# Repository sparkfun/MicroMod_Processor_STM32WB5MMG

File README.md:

SparkFun MicroMod Processor Board - STM32WB5MMG 
========================================

[*MicroMod Processor Board - STM32WB5MMG (DEV-21438)*](https://www.sparkfun.com/products/21438)

The MicroMod STM32WB5MMG Processor expands on SparkFun&apos;s MicroMod ST product line with a powerful combination of computing and wireless capabilities all on one Processor. The STM32WB5MMG from STMicroelectronics<sup>&trade;</sup> is an ultra-low power microcontroller that combines a pair of Arm<sup>&reg;</sup> Cortex<sup>&reg;</sup> processors; a Cortex-M4 processor for primary computing and a Cortex-M0 to run the 2.4 GHz radio. The radio is Bluetooth<sup>&reg;</sup> Low Energy 5.3, Zigbee<sup>&reg;</sup> 3.0, and OpenThread certified.

Repository Contents
-------------------

* **/Documentation** - Data sheets, additional product information
* **/Firmware** - Example code 
* **/Hardware** - Eagle design files (.brd, .sch)
* **/Production** - Production panel files (.brd)

Documentation
--------------
* **[Hookup Guide](https://learn.sparkfun.com/tutorials/micromod-stm32wb5mmg-hookup-guide)** - Basic hookup guide for the MicroMod Processor Board - STM32WB5MMG .
* **[SparkFun Fritzing repo](https://github.com/sparkfun/Fritzing_Parts)** - Fritzing diagrams for SparkFun products.
* **[SparkFun Graphical Datasheets](https://github.com/sparkfun/Graphical_Datasheets)** -Graphical Datasheets for various SparkFun products.

Product Versions
----------------
* [DEV-21438](https://www.sparkfun.com/products/21438)- MicroMod Processor for the STM32WB5MMG

License Information
-------------------

This product is _**open source**_! 

Please review the LICENSE.md file for license information. 

If you have any questions or concerns on licensing, please contact technical support on our [SparkFun forums](https://forum.sparkfun.com/viewforum.php?f=152).

Distributed as-is; no warranty is given.

- Your friends at SparkFun.

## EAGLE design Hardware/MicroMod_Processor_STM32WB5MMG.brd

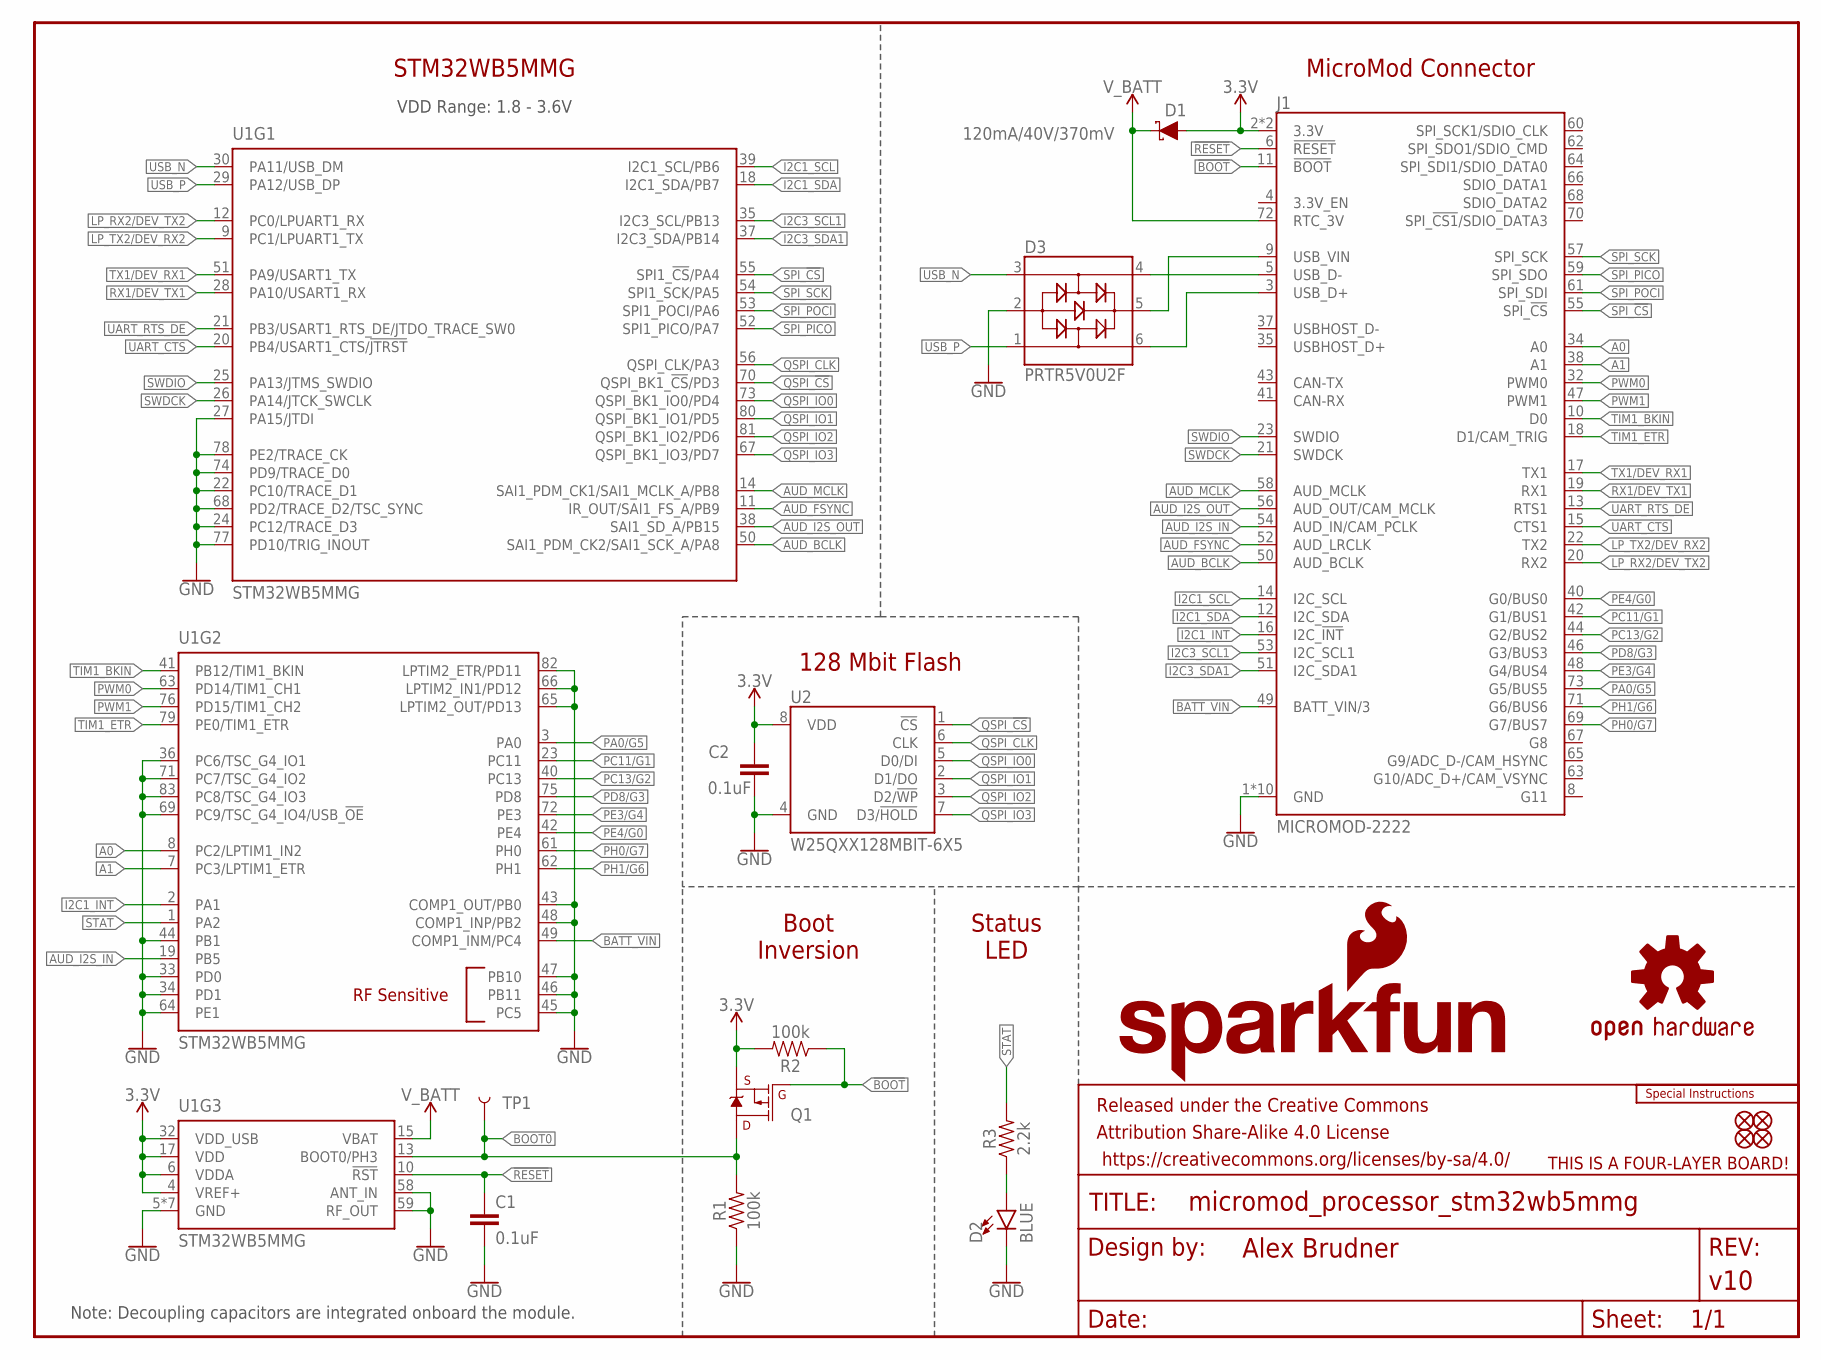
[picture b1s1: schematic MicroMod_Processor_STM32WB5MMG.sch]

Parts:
C1, C2: 0.1uF; 0402-TIGHT
D1: 120mA/40V/370mV; SOD-523
D2: BLUE; LED-0603
D3: PRTR5V0U2F; SOT886
FD1, FD2, FD3, FD4: FIDUCIALUFIDUCIAL; FIDUCIAL-MICRO
FRAME2: FRAME-LETTER; CREATIVE_COMMONS
J1: MICROMOD-2222; M.2-CARD-E-22
LOGO1: FOUR_LAYER_WARNING
LOGO2: OSHW-LOGOMINI; OSHW-LOGO-MINI
LOGO3: SFE_LOGO_NAME_FLAME.1_INCH; SFE_LOGO_NAME_FLAME_.1
LOGO4: SPECIAL_INSTRUCTIONS-ORDERING; ORDERING_INSTRUCTIONS
Q1: 20V/4.2A/52mΩ/1.4W; SOT23-3
R1, R2: 100k; 0402-TIGHT
R3: 2.2k; 0402-TIGHT
TP1: TEST-POINT3; PAD.03X.03
U1: STM32WB5MMG; SIP-LGA86
U2: W25QXX128MBIT-6X5; WSON-8-6X5

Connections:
3.3V: C2.1, D1.A, J1.2 (3.3V), J1.74 (3.3V), Q1.2 (S), R2.2, U1.4 (VREF+), U1.6 (VDDA), U1.17 (VDD), U1.32 (VDD_USB), U2.8 (VDD)
!BOOT!: J1.11 (!BOOT!), Q1.1 (G), R2.1
!RESET!: C1.1, J1.6 (!RESET!), U1.10 (!RST!)
A0: J1.34 (A0), U1.8 (PC2/LPTIM1_IN2)
A1: J1.38 (A1), U1.7 (PC3/LPTIM1_ETR)
AUD_BCLK: J1.50 (AUD_BCLK), U1.50 (SAI1_PDM_CK2/SAI1_SCK_A/PA8)
AUD_FSYNC: J1.52 (AUD_LRCLK), U1.11 (IR_OUT/SAI1_FS_A/PB9)
AUD_I2S_IN: J1.54 (AUD_IN/CAM_PCLK), U1.19 (PB5)
AUD_I2S_OUT: J1.56 (AUD_OUT/CAM_MCLK), U1.38 (SAI1_SD_A/PB15)
AUD_MCLK: J1.58 (AUD_MCLK), U1.14 (SAI1_PDM_CK1/SAI1_MCLK_A/PB8)
BATT_VIN: J1.49 (BATT_VIN/3), U1.49 (COMP1_INM/PC4)
BOOT0: Q1.3 (D), R1.2, TP1.1, U1.13 (BOOT0/PH3)
GND: C1.2, C2.2, D2.C, D3.2, J1.1 (GND), J1.7 (GND), J1.33 (GND), J1.36 (GND), J1.39 (GND), J1.45 (GND), J1.75 (GND), J1.GND1 (GND), J1.GND2 (GND), J1.GND3 (GND), R1.1, U1.5 (GND), U1.16 (GND), U1.22 (PC10/TRACE_D1), U1.24 (PC12/TRACE_D3), U1.27 (PA15/JTDI), U1.31 (GND), U1.33 (PD0), U1.34 (PD1), U1.36 (PC6/TSC_G4_IO1), U1.43 (COMP1_OUT/PB0), U1.44 (PB1), U1.45 (PC5), U1.46 (PB11), U1.47 (PB10), U1.48 (COMP1_INP/PB2), U1.57 (GND), U1.58 (ANT_IN), U1.59 (RF_OUT), U1.60 (GND), U1.64 (PE1), U1.65 (LPTIM2_OUT/PD13), U1.66 (LPTIM2_IN1/PD12), U1.68 (PD2/TRACE_D2/TSC_SYNC), U1.69 (PC9/TSC_G4_IO4/USB_!OE!), U1.71 (PC7/TSC_G4_IO2), U1.74 (PD9/TRACE_D0), U1.77 (PD10/TRIG_INOUT), U1.78 (PE2/TRACE_CK), U1.82 (LPTIM2_ETR/PD11), U1.83 (PC8/TSC_G4_IO3), U1.84 (GND), U1.86 (GND), U2.4 (GND)
I2C1_INT: J1.16 (I2C_!INT!), U1.2 (PA1)
I2C1_SCL: J1.14 (I2C_SCL), U1.39 (I2C1_SCL/PB6)
I2C1_SDA: J1.12 (I2C_SDA), U1.18 (I2C1_SDA/PB7)
I2C3_SCL1: J1.53 (I2C_SCL1), U1.35 (I2C3_SCL/PB13)
I2C3_SDA1: J1.51 (I2C_SDA1), U1.37 (I2C3_SDA/PB14)
LP_RX2/DEV_TX2: J1.20 (RX2), U1.12 (PC0/LPUART1_RX)
LP_TX2/DEV_RX2: J1.22 (TX2), U1.9 (PC1/LPUART1_TX)
unnamed: D2.A, R3.1
unnamed: D3.5, J1.9 (USB_VIN)
PA0/G5: J1.73 (G5/BUS5), U1.3 (PA0)
PC11/G1: J1.42 (G1/BUS1), U1.23 (PC11)
PC13/G2: J1.44 (G2/BUS2), U1.40 (PC13)
PD8/G3: J1.46 (G3/BUS3), U1.75 (PD8)
PE3/G4: J1.48 (G4/BUS4), U1.72 (PE3)
PE4/G0: J1.40 (G0/BUS0), U1.42 (PE4)
PH0/G7: J1.69 (G7/BUS7), U1.61 (PH0)
PH1/G6: J1.71 (G6/BUS6), U1.62 (PH1)
PWM0: J1.32 (PWM0), U1.63 (PD14/TIM1_CH1)
PWM1: J1.47 (PWM1), U1.76 (PD15/TIM1_CH2)
QSPI_!CS!: U1.70 (QSPI_BK1_!CS!/PD3), U2.1 (!CS!)
QSPI_CLK: U1.56 (QSPI_CLK/PA3), U2.6 (CLK)
QSPI_IO0: U1.73 (QSPI_BK1_IO0/PD4), U2.5 (D0/DI)
QSPI_IO1: U1.80 (QSPI_BK1_IO1/PD5), U2.2 (D1/DO)
QSPI_IO2: U1.81 (QSPI_BK1_IO2/PD6), U2.3 (D2/!WP!)
QSPI_IO3: U1.67 (QSPI_BK1_IO3/PD7), U2.7 (D3/!HOLD!)
RX1/DEV_TX1: J1.19 (RX1), U1.28 (PA10/USART1_RX)
SPI_!CS!: J1.55 (SPI_!CS!), U1.55 (SPI1_!CS!/PA4)
SPI_PICO: J1.59 (SPI_SDO), U1.52 (SPI1_PICO/PA7)
SPI_POCI: J1.61 (SPI_SDI), U1.53 (SPI1_POCI/PA6)
SPI_SCK: J1.57 (SPI_SCK), U1.54 (SPI1_SCK/PA5)
STAT: R3.2, U1.1 (PA2)
SWDCK: J1.21 (SWDCK), U1.26 (PA14/JTCK_SWCLK)
SWDIO: J1.23 (SWDIO), U1.25 (PA13/JTMS_SWDIO)
TIM1_BKIN: J1.10 (D0), U1.41 (PB12/TIM1_BKIN)
TIM1_ETR: J1.18 (D1/CAM_TRIG), U1.79 (PE0/TIM1_ETR)
TX1/DEV_RX1: J1.17 (TX1), U1.51 (PA9/USART1_TX)
UART_CTS: J1.15 (CTS1), U1.20 (PB4/USART1_CTS/!JTRST!)
UART_RTS_DE: J1.13 (RTS1), U1.21 (PB3/USART1_RTS_DE/JTDO_TRACE_SW0)
USBIN_N: D3.4, J1.5 (USB_D-)
USBIN_P: D3.6, J1.3 (USB_D+)
USB_N: D3.3, U1.30 (PA11/USB_DM)
USB_P: D3.1, U1.29 (PA12/USB_DP)
V_BATT: D1.C, J1.72 (RTC_3V), U1.15 (VBAT)

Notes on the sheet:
Note: Decoupling capacitors are integrated onboard the module.
VDD Range: 1.8 - 3.6V
STM32WB5MMG
MicroMod Connector
128 Mbit Flash
Boot Inversion
Status LED

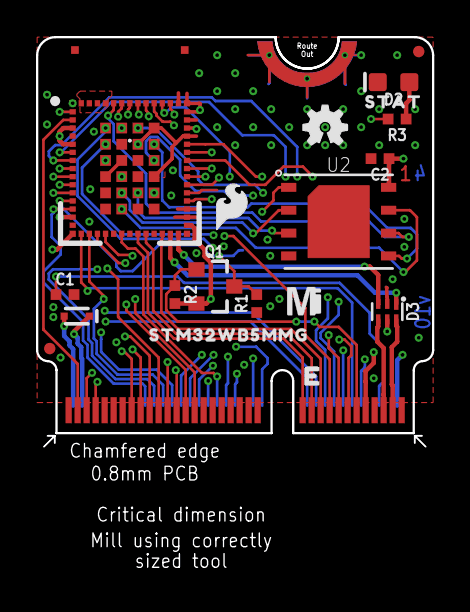
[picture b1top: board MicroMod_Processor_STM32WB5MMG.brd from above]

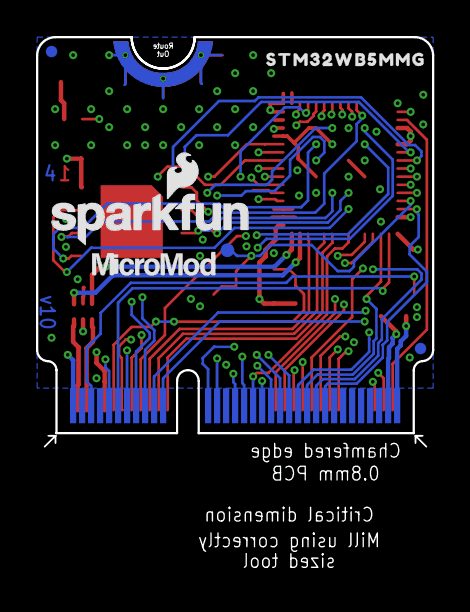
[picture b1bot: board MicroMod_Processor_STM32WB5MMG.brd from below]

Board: 4 copper layers, 22.0 x 22.8 mm, 29 parts (7 on the bottom side), 56 nets.

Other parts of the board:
U$1: MICROMOD_MI_LOGO_.35
U$2: MICROMOD_LOGO_.3
U$3: SFE_LOGO_FLAME_.1
U$4, U$5: STM32WB5MMG0
U$6: SFE_LOGO_FLAME_STOP_.1
U$7: STAT0

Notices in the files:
parts and their libraries:
SparkFun-Aesthetics: Licensing: Creative Commons ShareAlike 4.0 International - https://creativecommons.org/licenses/by-sa/4.0
SparkFun-Aesthetics: Released under the Creative Commons Attribution Share-Alike 4.0 License
SparkFun-Aesthetics: https://creativecommons.org/licenses/by-sa/4.0
